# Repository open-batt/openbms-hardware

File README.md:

# OpenBMS

OpenBMS is an **open-source battery management system** for 2 to 7-cell Li-Ion and Li-Po battery packs. A fully integrated hardware and firmware solution for battery management and protection, providing:
-  **Fuel gauge** — measure battery capacity, state of charge, and state of health
-  **Learning algorithms** — learn battery behavior and adjust management accordingly
-  **Cell balancing** — keep multi-cell voltages in sync to prevent drift over time
-  **Protection** — guard against overcharging, overdischarging, overheating, and short circuits
-  **Communication** — talk to chargers, displays, microcontrollers, and other devices

<table>
  <tr>
    <td></td>
    <td></td>
  </tr>
</table>

## Rev B is out!
Schematic and layout updated, fixes applied

## Related repositories

[OpenBMS-firmware](https://github.com/open-batt/openbms-firmware)  
[OpenBMS-test-bench](https://github.com/open-batt/openbms-test-bench-hardware)  
[OpenBMS-studio](https://github.com/open-batt/openbms-studio)

## How OpenBMS fits into system?

Battery system consists of:
- **Li-ion/Li-Po battery** — your custom 2- to 7-cell battery
- **OpenBMS** — battery management system that handles fuel gauging, cell balancing, learning algorithms, overcharge/overdischarge/overheat protection, and communication with chargers and microcontrollers
- [**Test Bench**](https://github.com/open-batt/openbms-test-bench-hardware) — a 600W dissipative resistive load for easier BMS development and testing
- **Host** — I2C/CAN interfaces, wake-up signal, can be a microcontroller, computer, etc.
- **Charger** — your custom charger, usually a CC/CV charger adjusted to your battery voltage and current
- [**OpenBMS Studio**](https://github.com/open-batt/openbms-studio) — a PC software for configuring and monitoring the BMS, visualizing data, and updating firmware using UART communication

<br/>

<video width="100%" autoplay muted loop playsinline>
  <source src="images_videos/video_2.mp4" type="video/mp4" />
</video>

## ❤️ Funding

This project is funded through [NGI0 Commons Fund](https://nlnet.nl/commonsfund), a fund established by [NLnet](https://nlnet.nl) with financial support from the European Commission's [Next Generation Internet](https://ngi.eu) program. 

We are very grateful to the NLnet team for helping us on our path, and we encourage you too to apply and get funds to build your project! 🚀
Learn more at the [NLnet project page](https://nlnet.nl/project/OpenBMS).

## ⚠️ Status: Work in progress

| Module | Status |
|--------|--------|
| OpenBMS Schematics & PCB Layout Rev A| ✅ Done |
| OpenBMS Test Bench Schematic & PCB Layout | ✅ Done |
| Revision B (Hardware improvements) |  ✅ Done |
| BMS, Test Bench & Battery Tests |  🚧 In progress |
| Documentation & Final Release | 🚧 In progress |

## Features

- 🔋 Supports pack voltages up to 30V and continuous currents up to 16A.
- ⚡ State of Charge (SoC) estimation using coulomb counting
- 🩺 State of Health (SoH) monitoring with capacity fade tracking and internal resistance estimation
- 📊 Per-cell voltage monitoring with 24-bit resolution
- 🔌 Pack and cell overcurrent protection up to 20A hardware trip (adjustable threshold)
- 🛡️ Overvoltage and undervoltage protection (adjustable thresholds)
- 🔀 Passive cell balancing for up to 7 cells
- 🔵 Battery current measurement via precision shunt resistor
- 🌡️ NTC thermistor input for battery temperature monitoring
- 🌡️ On-board ambient temperature monitoring via MCU and ADC internal sensors
- 💾 Non-volatile storage of SoC, SoH, impedance, fault history, and charge profiles (EEPROM)
- 🚌 CAN bus communication interface (up to 1 Mbit/s)
- 🔗 I2C communication interface for host integration (SMBus compatible)
- 🖥️ UART debug interface
- 🔔 Wake-up input with power-on latch for low-power system control
- 🔋 Power-down mode quiescent current < 2 µA
- 🖥️ Based on STM32L431 ARM Cortex-M4 microcontroller
  
## Overview
First, a small introduction to the project structure:
```
+-------------+       +---------------------------+       +----------------+
|             |       |         OpenBMS           |       |                |
|   Battery   |       | - - - - - - - - - - - - - |       |     System     |
| 2-7S Li-Ion | cells |   +-------+   +-------+   |       |                |
| 2-7S Li-Po  |- - - >|   |  ADC  |   |  MCU  |   |<----->|    host/load   |
|             |       |   +-------+   +-------+   | comms |                |
|             |<=====>|   +-------+   +-------+   |<=====>|     Charger    |
|             |  pwr  |   | Power |   | FETs  |   |  pwr  |                |
+-------------+       |   +-------+   +-------+   |       +----------------+
                       +-----------+--------------+
```

OpenBMS and the battery are designed to be a single, inseparable unit. Ideally, it is
connected on the first day of the battery's life and stays throughout its entire lifetime.
This way, OpenBMS learns the battery's characteristics over time and continuously tracks
its state of health and other parameters.
 
It protects the battery from overcurrent, overvoltage, and undervoltage conditions, and
balances cells to maximize pack lifetime. State of charge estimation tells you exactly how
much energy you have left, while long-term health monitoring tells you when it's time to
replace the battery.
 
The battery communicates with the host system via CAN bus or I2C. Through OpenBMS, the battery can:
- Give energy to the system (discharge)
- Take energy from the system (charge)
 
OpenBMS can be easily described with the following block diagram:

```
+---------------------------------------------------------------------------------------------------------------+
|                                                  OpenBMS                                                      |
|                                                                                                               |
|  +-----------------------+     power     +-------------------+     power     +-------------------------+      |
|  |    Battery Input      |<=============>|  Switch Circuit   |<=============>|         Output          |      |
|  | - - - - - - - - - - - |               | - - - - - - - - - |               | - - - - - - - - - - - - |      |
|  | + XT60 pwr connector  |               | + Main NFETs      |               | + XT60 pwr connector    |      |
|  | + 8-pin JST (balancer)|               | + Precharge FETs  |               | + JST (I2C,CAN,WAKE_UP) |      |
|  | + 2-pin JST (NTC)     |               +--------+----------+               +-------------------------+      |
|  +-----------------------+                         |                                      ^                   |
|            |                                       | ctr signals                          | can, i2c, wake_up |
|            | cells                                 v                                      |                   |
|  +---------------------+       SPI      +-------------------------+                       |                   |
|  |    Analog Block     |<==============>|     Digital Block       |=======================+                   |
|  |     (ADS131M08)     |                | - - - - - - - - - - - - |                                           |
|  | - - - - - - - - - - |                | + STM32L431 (Cortex-M4) |                                           |
|  | + Cell voltage x7   |                | + EEPROM                |                                           |
|  | + Pack voltage      |                | + LED indicators        |                                           |
|  | + Current           |                | + SWD / UART debug      |                                           |
|  | + PFETs cell switch |                | + I2C / CANinterfaces   |                                           |
|  +---------------------+                +-------------------------+                                           |
|                                                     ^                                                         |
|                                                     | 3.3V, wake_up                                           |
|                                          +----------+---------+                                               |
|                                          | 3.3V Power Supply  |                                               |
|                                          | - - - - - - - - -  |                                               |
|                                          | + Buck converter   |                                               |
|                                          | + Enable latch     |                                               |
|                                          +--------------------+                                               |
|                                                                                                               |
+---------------------------------------------------------------------------------------------------------------+
```

## Characteristics

| Parameter                                    | Value                                             |
|----------------------------------------------|---------------------------------------------------|
| Cell count                                   | 2 to 7 cells                                      |
| Supported chemistries                        | Li-Ion, Li-Po                                     |
| Communication interfaces                     | CAN bus (up to 1 Mbit/s), I2C (SMBus compatible)  |
| Maximum pack voltage                         | 30.1V (7 cells × 4.3V)                            |
| Minimum pack voltage                         | 4V (2 cells × 2V)                                 |
| Maximum continuous current                   | 16A                                               |
| Maximum peak current                         | 20A (hardware trip)                               |
| Current consumption (active, 7-cell, max)    | 6mA                                               |
| Current consumption (active, 7-cell, typ)    | 4mA                                               |
| Current consumption (active, 2-cell, max)    | 19mA                                              |
| Current consumption (active, 2-cell, typ)    | 13mA                                              |
| Power-down quiescent current                 | < 2 µA                                            |
| Operating temperature range                  | -40°C to 85°C                                     |

## License

OpenBMS is licensed under the MIT license and CERN OHL-S v2.

Check [openbatt.dev](https://openbatt.dev) for more!

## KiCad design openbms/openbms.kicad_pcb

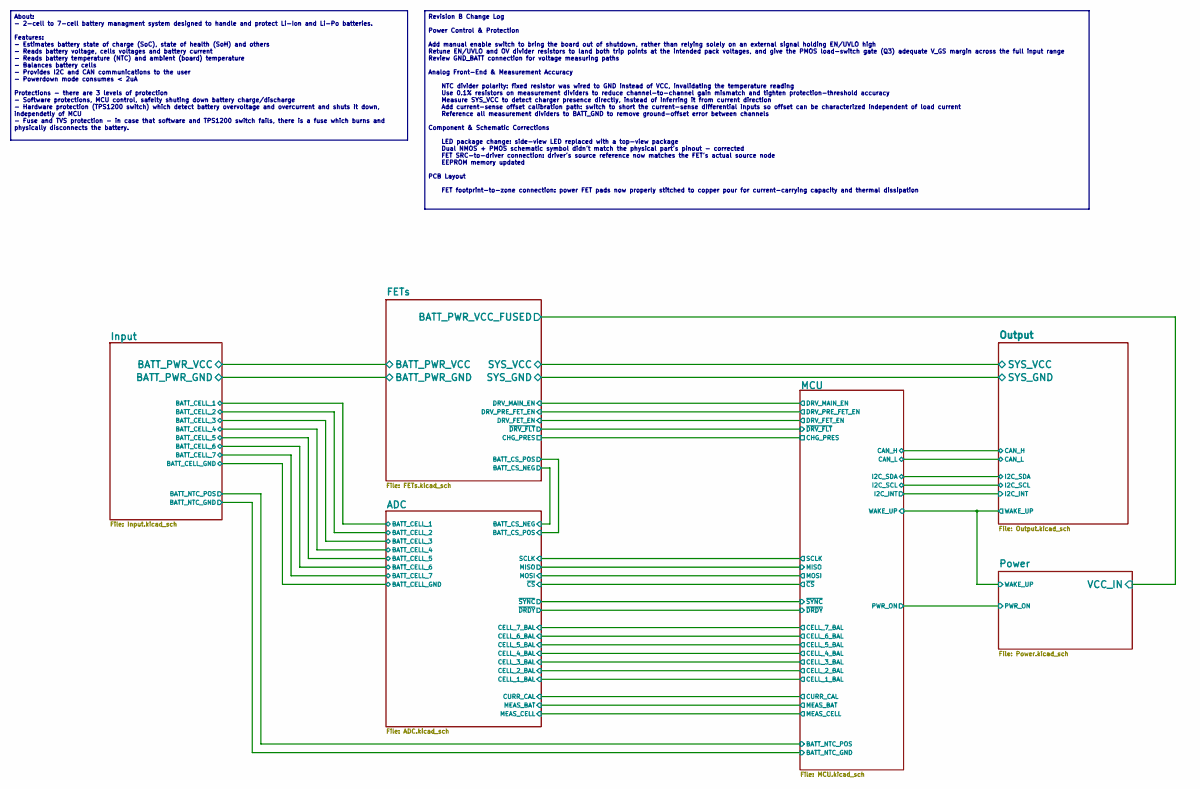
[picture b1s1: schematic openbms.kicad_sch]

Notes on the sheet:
About: - 2-cell to 7-cell battery managment system designed to handle and protect Li-Ion and Li-Po batteries. Features: - Estimates battery state of charge (SoC), state of health (SoH) and others - Reads battery voltage, cells voltages and battery current - Reads battery temperature (NTC) and ambie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
Revision B Change Log Power Control & Protection Add manual enable switch to bring the board out of shutdown, rather than relying solely on an external signal holding EN/UVLO high Retune EN/UVLO and OV divider resistors to land both trip points at the intended pack voltages, and give the PMOS load-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

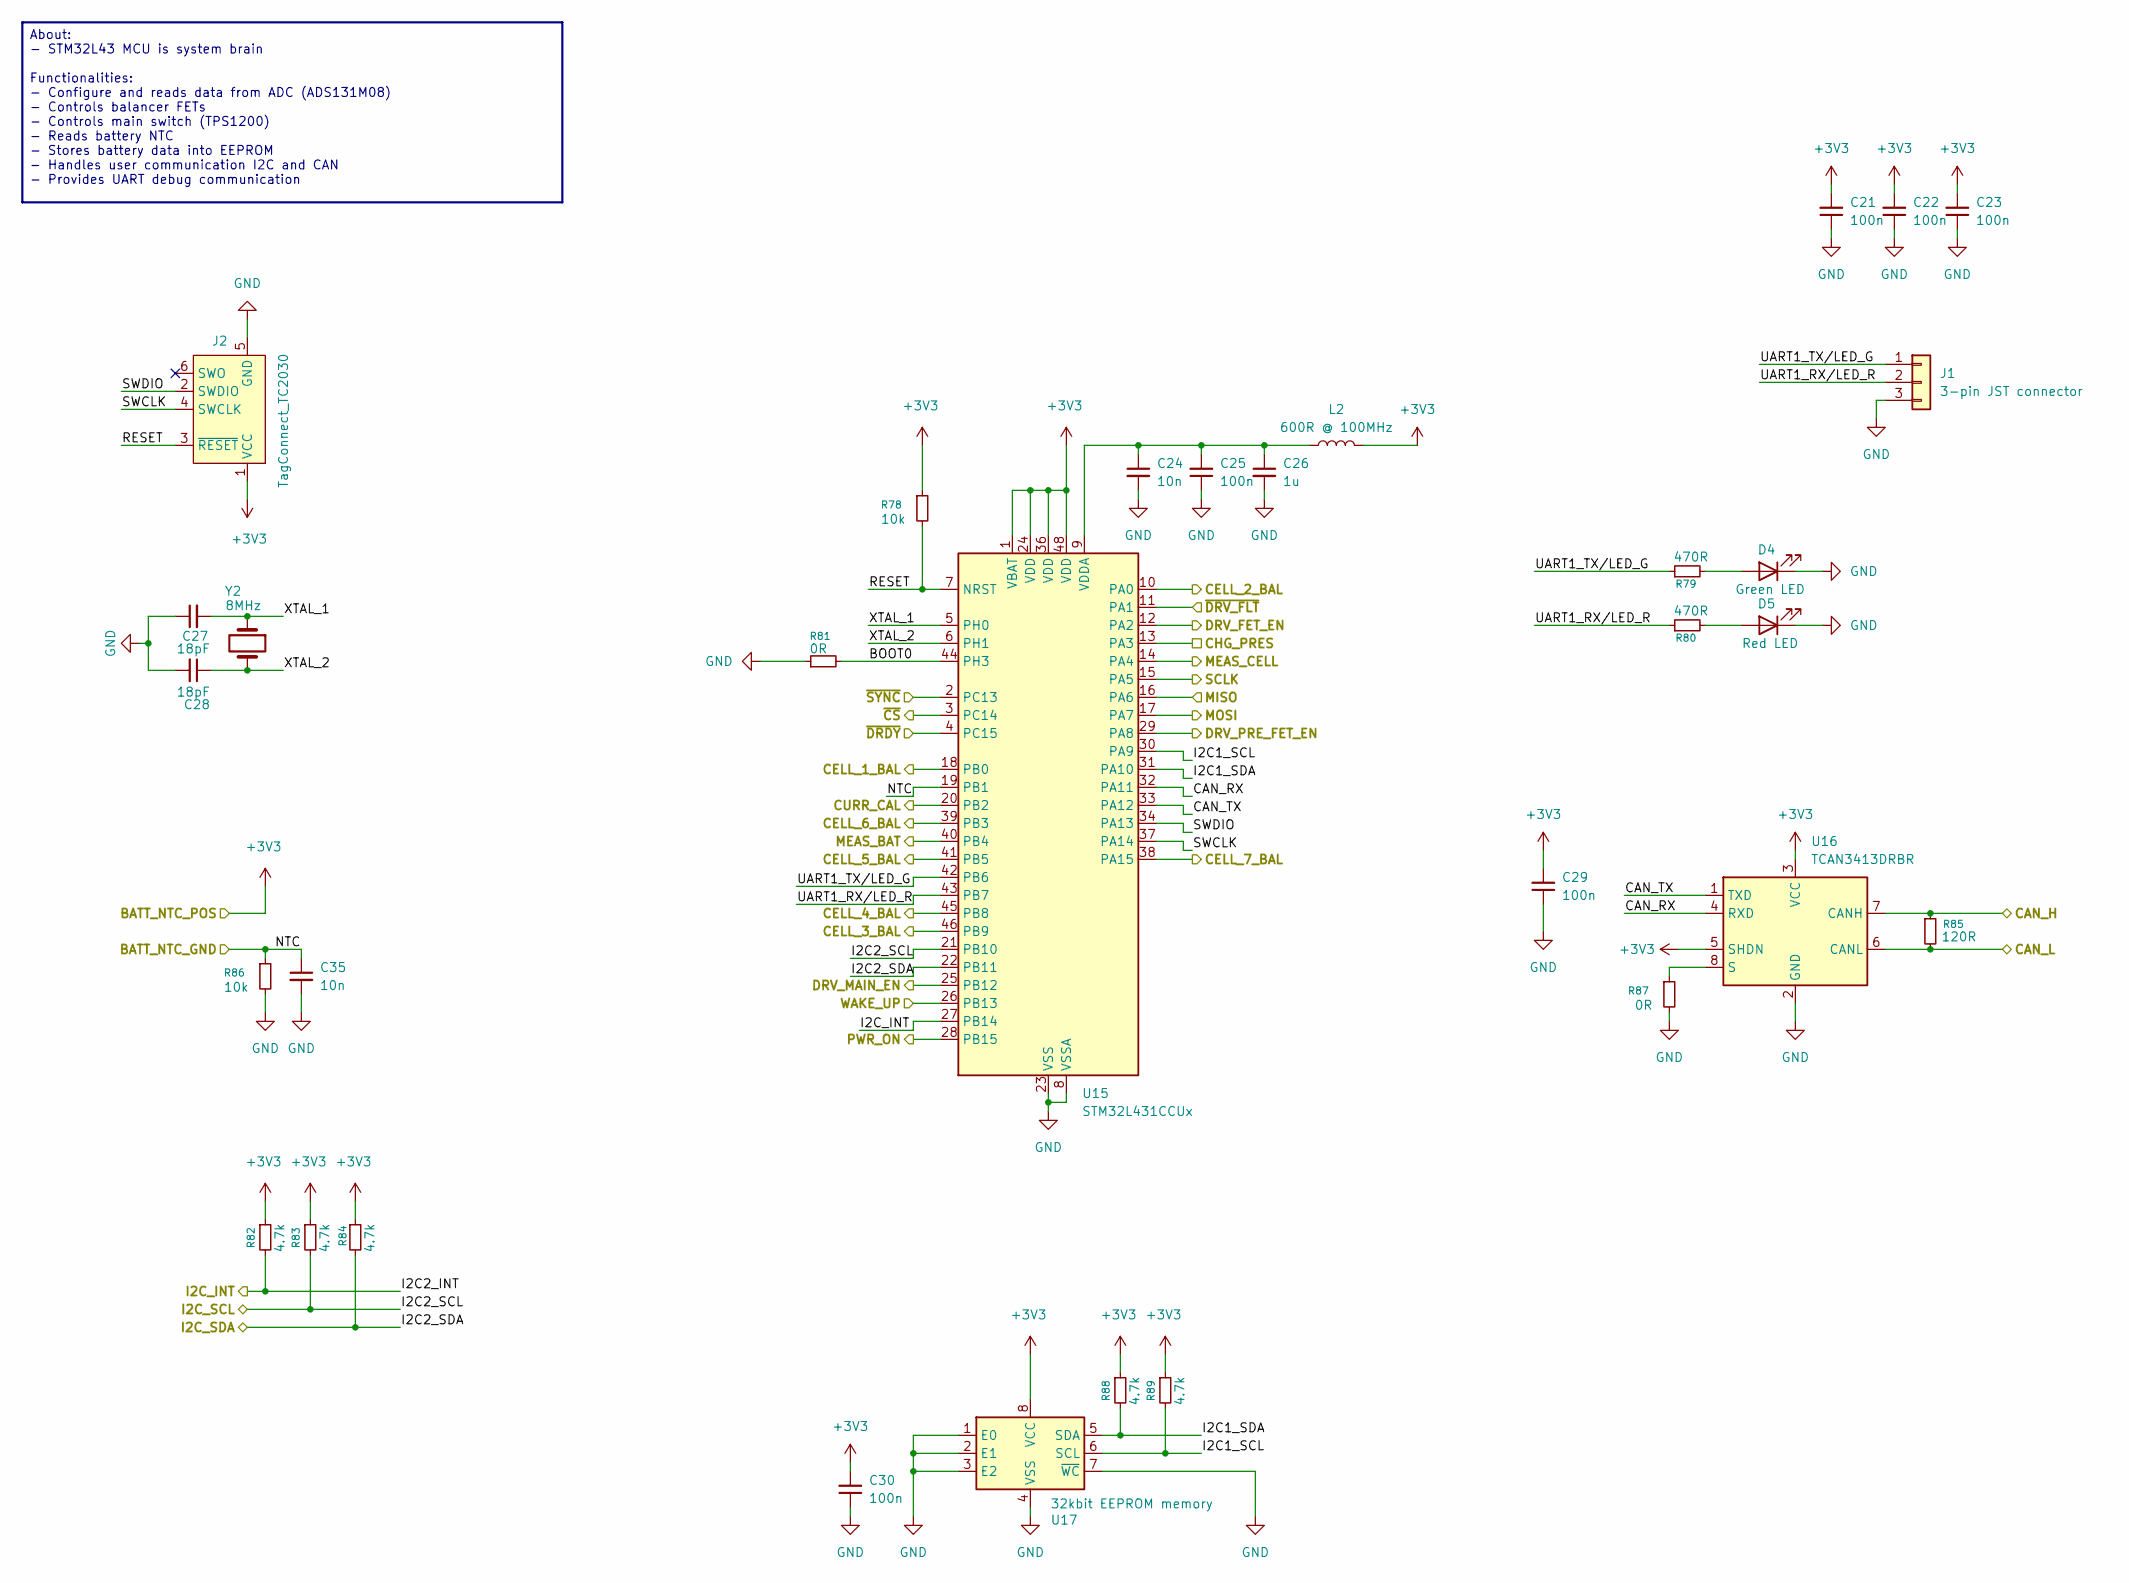
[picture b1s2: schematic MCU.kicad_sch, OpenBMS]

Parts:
C21, C22, C23, C25, C29, C30: 100n; C_0402_1005Metric; Manufacturer_Part_Number GRM155R71A104KA01D
C24, C35: 10n; C_0402_1005Metric; Manufacturer_Part_Number C0402C103K5REC7411
C26: 1u; C_0402_1005Metric; Manufacturer_Part_Number C0402C105K8PACTU
C27, C28: 18pF; C_0402_1005Metric; Manufacturer_Part_Number GRM1555C1H180JA01D
D4: Green LED; LED_0603_1608Metric; Manufacturer_Part_Number LTST-C190GKT
D5: Red LED; LED_0603_1608Metric; Manufacturer_Part_Number LTST-C190KRKT
J1: 3-pin JST connector; JST_GH_BM03B-GHS-TBT_1x03-1MP_P1.25mm_Vertical; Manufacturer_Part_Number BM03B-GHS-TBT
J2: TagConnect_TC2030; Tag-Connect_TC2030-IDC-FP_2x03_P1.27mm_Vertical
L2: 600R @ 100MHz; L_0402_1005Metric; Manufacturer_Part_Number BLM15PX601SN1D
R78, R86: 10k; R_0402_1005Metric; Manufacturer_Part_Number RMCF0402FT10K0
R79, R80: 470R; R_0402_1005Metric; Manufacturer_Part_Number RC0402FR-07470RL
R81, R87: 0R; R_0402_1005Metric; Manufacturer_Part_Number CR0402AJ/-000GAS
R82, R83, R84, R88, R89: 4.7k; R_0402_1005Metric; Manufacturer_Part_Number RC0402JR-074K7L
R85: 120R; R_0402_1005Metric; Manufacturer_Part_Number CRCW0402120RFKEDC
U15: STM32L431CCUx; QFN-48-1EP_7x7mm_P0.5mm_EP5.6x5.6mm; Manufacturer_Part_Number STM32L431CCU6TR
U16: TCAN3413DRBR; Manufacturer_Part_Number TCAN3413DRBR
U17: 32kbit EEPROM memory; SOIC-8_3.9x4.9mm_P1.27mm; Manufacturer_Part_Number M24256-DRMN8TP/K
Y2: 8MHz; ECS81921230QENTR; Manufacturer_Part_Number ECS-80-12-30Q-DS-TR

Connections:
+3V3: C21.2, C22.2, C23.2, C29.2, C30.2, J2.1 (VCC), L2.2, R78.1, R82.1, R83.1, R84.1, R88.1, R89.1, U15.1 (VBAT), U15.24 (VDD), U15.36 (VDD), U15.48 (VDD), U16.3 (VCC), U16.5 (SHDN), U17.8 (VCC); also elsewhere on the board
/ADC/CELL_1_BAL: U15.18 (PB0); also elsewhere on the board
/ADC/CELL_2_BAL: U15.10 (PA0); also elsewhere on the board
/ADC/CELL_3_BAL: U15.46 (PB9); also elsewhere on the board
/ADC/CELL_4_BAL: U15.45 (PB8); also elsewhere on the board
/ADC/CELL_5_BAL: U15.41 (PB5); also elsewhere on the board
/ADC/CELL_6_BAL: U15.39 (PB3); also elsewhere on the board
/ADC/CELL_7_BAL: U15.38 (PA15); also elsewhere on the board
/ADC/CURR_CAL: U15.20 (PB2); also elsewhere on the board
/ADC/MEAS_BAT: U15.40 (PB4); also elsewhere on the board
/ADC/MEAS_CELL: U15.14 (PA4); also elsewhere on the board
/ADC/MISO: U15.16 (PA6); also elsewhere on the board
/ADC/MOSI: U15.17 (PA7); also elsewhere on the board
/ADC/SCLK: U15.15 (PA5); also elsewhere on the board
/ADC/~CS: U15.3 (PC14); also elsewhere on the board
/ADC/~DRDY: U15.4 (PC15); also elsewhere on the board
/ADC/~SYNC: U15.2 (PC13); also elsewhere on the board
/FETs/CHG_PRES: U15.13 (PA3); also elsewhere on the board
/FETs/DRV_FET_EN: U15.12 (PA2); also elsewhere on the board
/FETs/DRV_MAIN_EN: U15.25 (PB12); also elsewhere on the board
/FETs/DRV_PRE_FET_EN: U15.29 (PA8); also elsewhere on the board
/FETs/~DRV_FLT: U15.11 (PA1); also elsewhere on the board
/MCU/BOOT0: R81.2, U15.44 (PH3)
/MCU/CAN_H: R85.1, U16.7 (CANH); also elsewhere on the board
/MCU/CAN_L: R85.2, U16.6 (CANL); also elsewhere on the board
/MCU/CAN_RX: U15.32 (PA11), U16.4 (RXD)
/MCU/CAN_TX: U15.33 (PA12), U16.1 (TXD)
/MCU/I2C1_SCL: R89.2, U15.30 (PA9), U17.6 (SCL)
/MCU/I2C1_SDA: R88.2, U15.31 (PA10), U17.5 (SDA)
/MCU/I2C2_INT: R82.2, U15.27 (PB14); also elsewhere on the board
/MCU/I2C2_SCL: R83.2, U15.21 (PB10); also elsewhere on the board
/MCU/I2C2_SDA: R84.2, U15.22 (PB11); also elsewhere on the board
/MCU/NTC: C35.1, R86.1, U15.19 (PB1); also elsewhere on the board
/MCU/PWR_ON: U15.28 (PB15); also elsewhere on the board
/MCU/RESET: J2.3 (~RESET), R78.2, U15.7 (NRST)
/MCU/SWCLK: J2.4 (SWCLK), U15.37 (PA14)
/MCU/SWDIO: J2.2 (SWDIO), U15.34 (PA13)
/MCU/WAKE_UP: U15.26 (PB13); also elsewhere on the board
/MCU/XTAL_1: C27.2, U15.5 (PH0), Y2.1
/MCU/XTAL_2: C28.1, U15.6 (PH1), Y2.2
GND: C21.1, C22.1, C23.1, C24.2, C25.1, C26.2, C27.1, C28.2, C29.1, C30.1, C35.2, D4.1 (K), D5.1 (K), J1.3, J2.5 (GND), R81.1, R86.2, R87.2, U15.8 (VSSA), U15.23 (VSS), U15.35 (VSS), U15.47 (VSS), U15.49 (VSS), U16.2 (GND), U17.1 (E0), U17.2 (E1), U17.3 (E2), U17.4 (VSS), U17.7 (~WC); also elsewhere on the board
unnamed: D4.2 (A), R79.2
unnamed: D5.2 (A), R80.2
unnamed: C24.1, C25.2, C26.1, L2.1, U15.9 (VDDA)
unnamed: R87.1, U16.8 (S)

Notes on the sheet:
About: - STM32L43 MCU is system brain Functionalities: - Configure and reads data from ADC (ADS131M08) - Controls balancer FETs - Controls main switch (TPS1200) - Reads battery NTC - Stores battery data into EEPROM - Handles user communication I2C and CAN - Provides UART debug communication

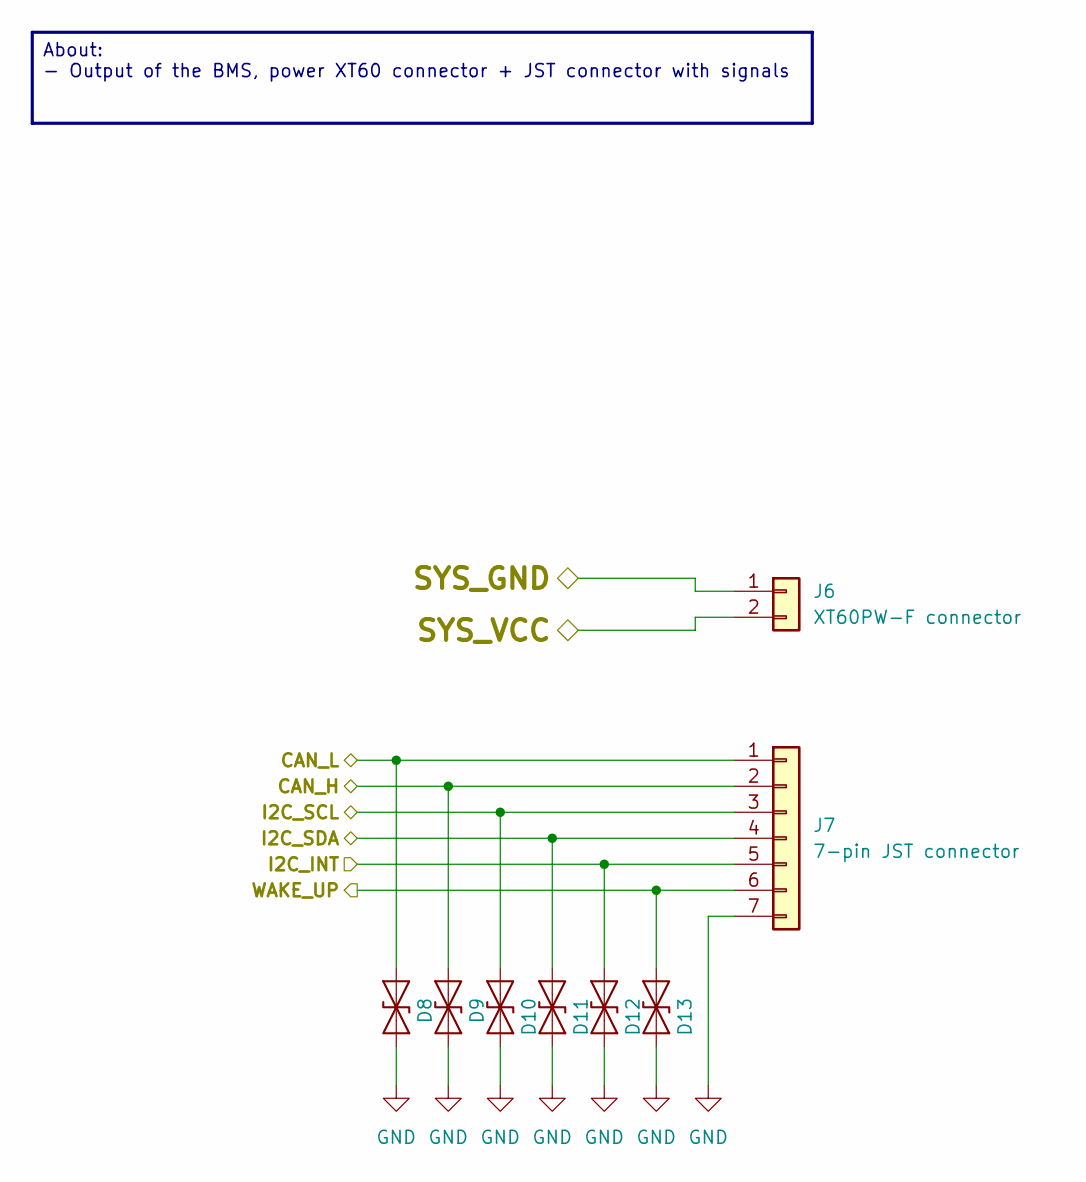
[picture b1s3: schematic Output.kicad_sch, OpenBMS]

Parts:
D8, D9, D10, D11, D12, D13: TVS diode DBLC03CIQ-7; D_SOD-323; Manufacturer_Part_Number DBLC03CIQ-7
J6: XT60PW-F connector; AMASS_XT60PW-F_1x02_P7.20mm_Horizontal; Manufacturer_Part_Number XT60PW-F
J7: 7-pin JST connector; JST_XH_S7B-XH-A_1x07_P2.50mm_Horizontal; Manufacturer_Part_Number S7B-XH-A

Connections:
/FETs/SYS_VCC: J6.2; also elsewhere on the board
/MCU/CAN_H: D9.1 (A1), J7.2; also elsewhere on the board
/MCU/CAN_L: D8.1 (A1), J7.1; also elsewhere on the board
/MCU/I2C2_INT: D12.1 (A1), J7.5; also elsewhere on the board
/MCU/I2C2_SCL: D10.1 (A1), J7.3; also elsewhere on the board
/MCU/I2C2_SDA: D11.1 (A1), J7.4; also elsewhere on the board
/MCU/WAKE_UP: D13.1 (A1), J7.6; also elsewhere on the board
GND: D8.2 (A2), D9.2 (A2), D10.2 (A2), D11.2 (A2), D12.2 (A2), D13.2 (A2), J7.7; also elsewhere on the board
SYS_GND: J6.1; also elsewhere on the board

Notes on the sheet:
About: - Output of the BMS, power XT60 connector + JST connector with signals

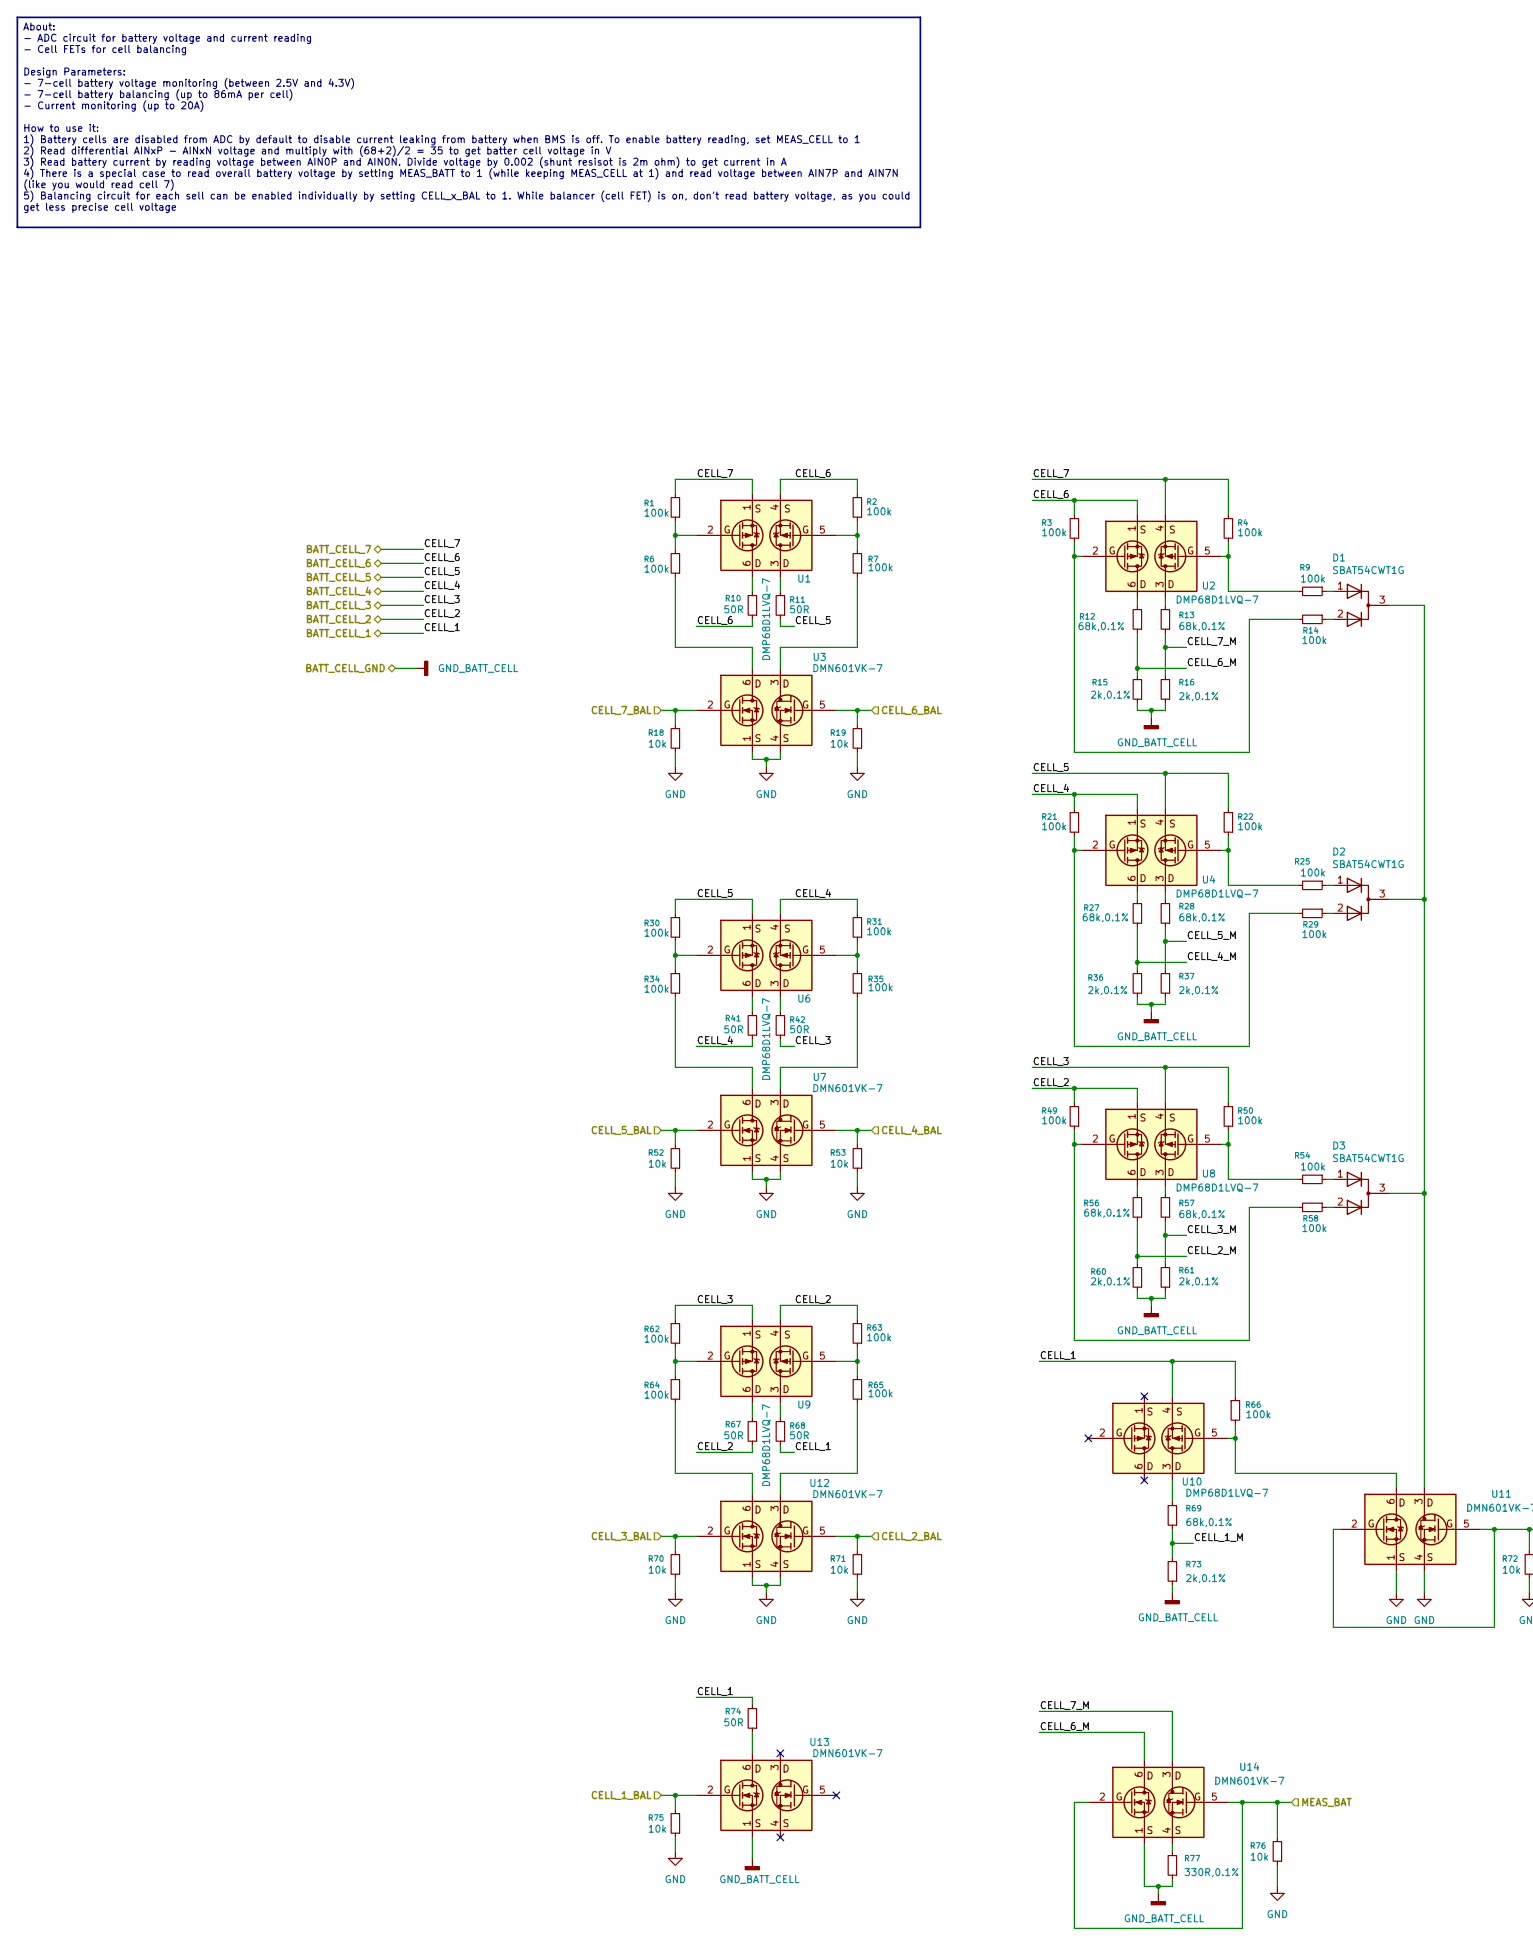
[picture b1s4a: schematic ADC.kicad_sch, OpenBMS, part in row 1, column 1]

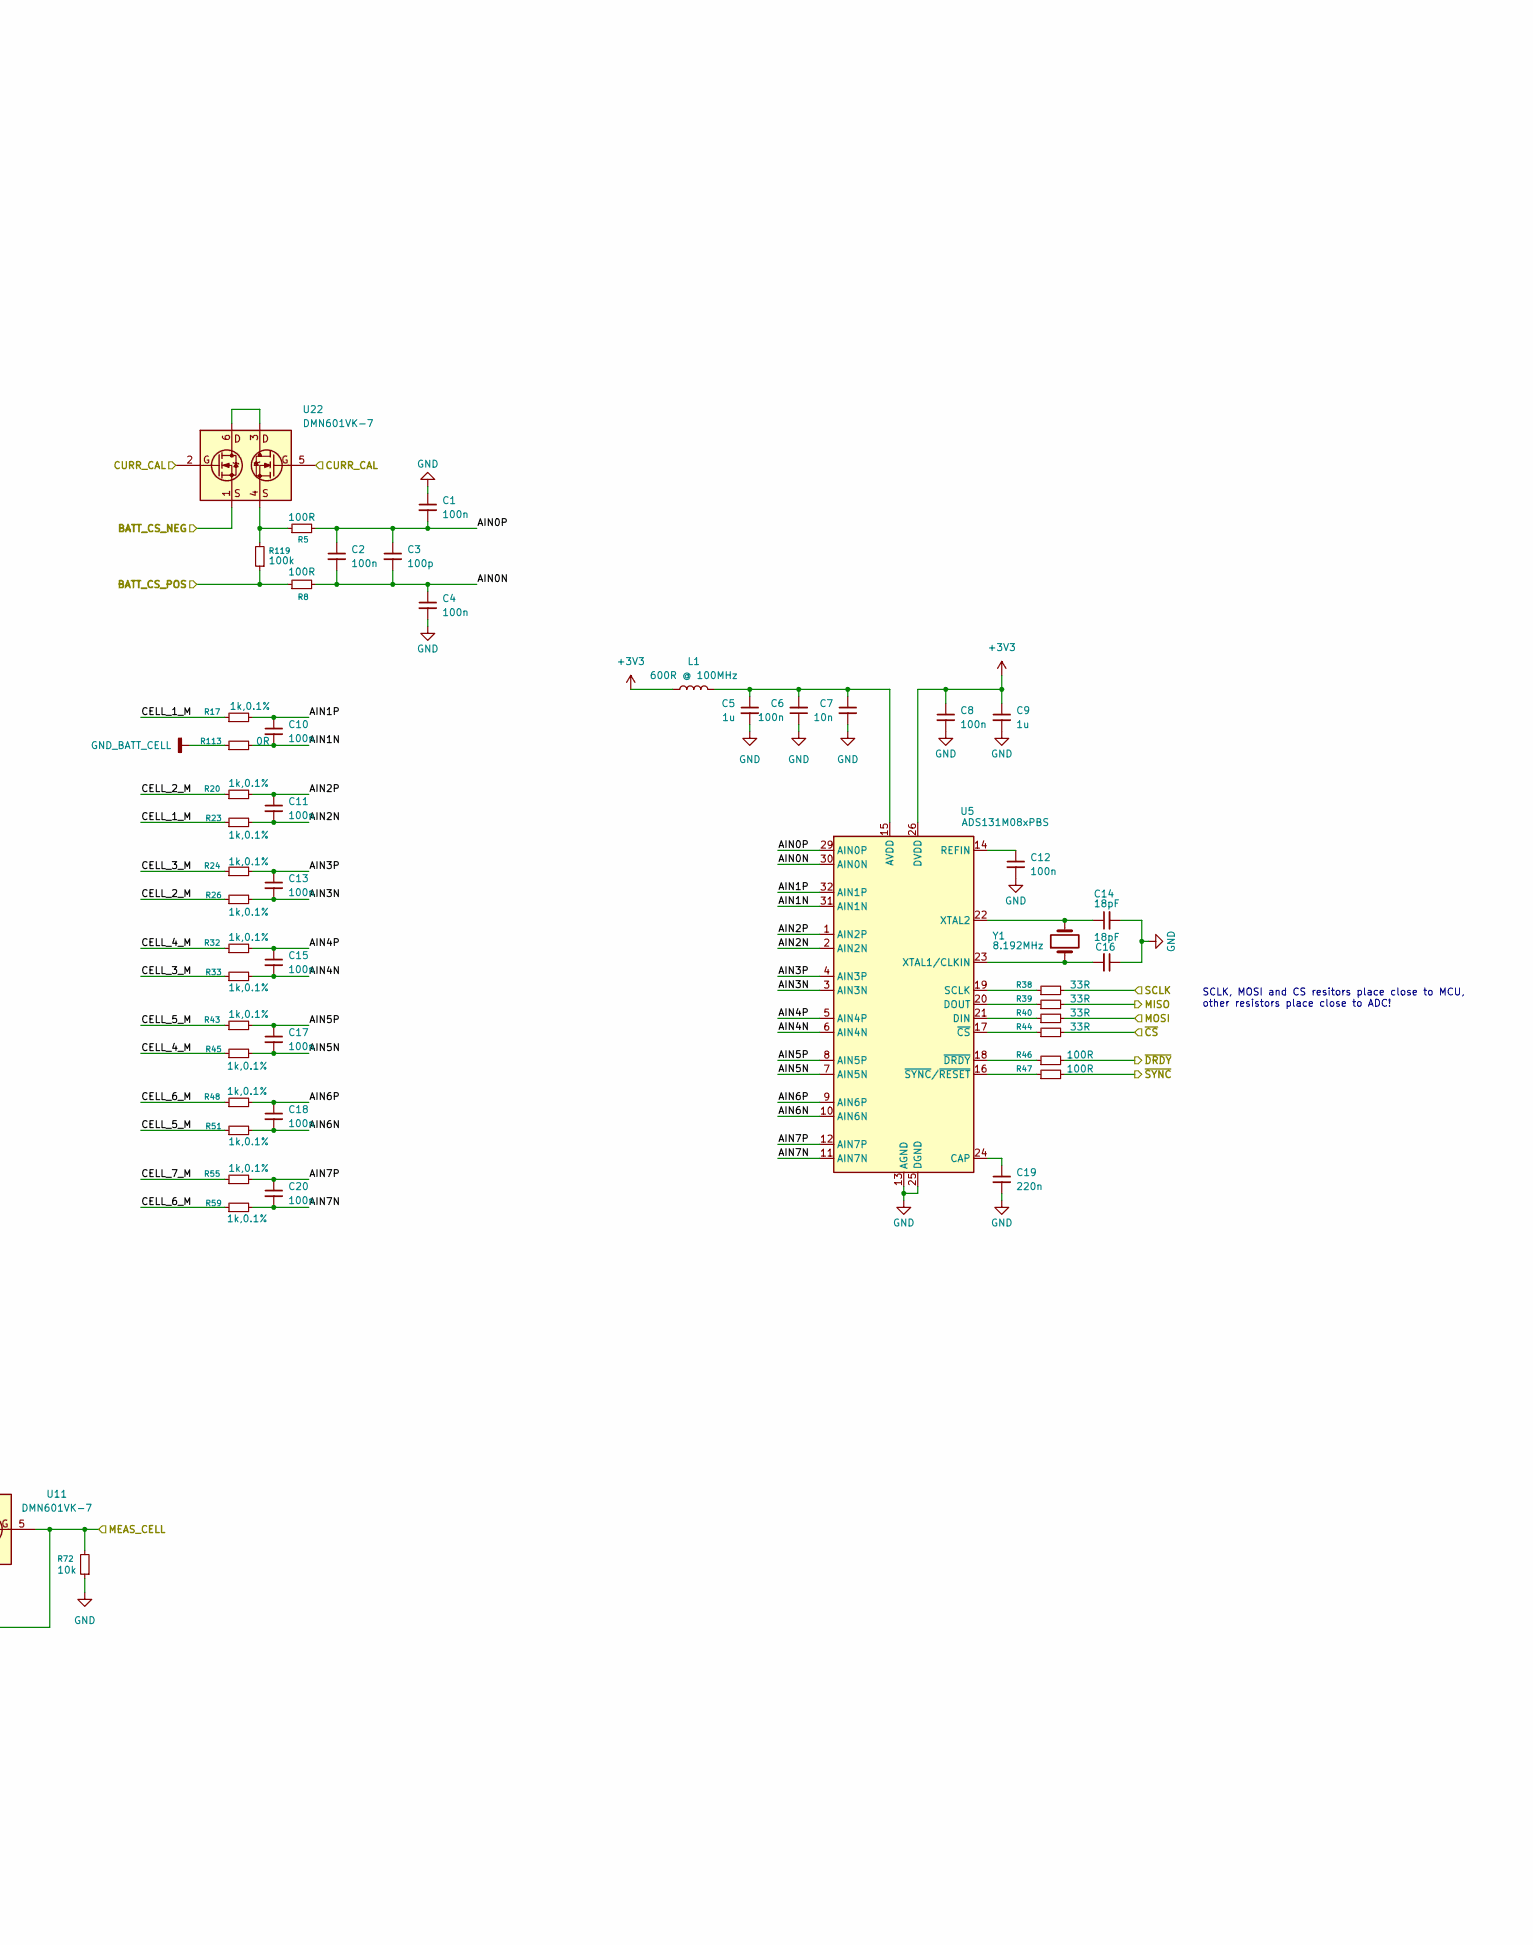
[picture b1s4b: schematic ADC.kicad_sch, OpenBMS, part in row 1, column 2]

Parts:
C1, C2, C4, C6, C8, C10, C11, C12, C13, C15, C17, C18, C20: 100n; C_0402_1005Metric; Manufacturer_Part_Number GRM155R71A104KA01D
C3: 100p; C_0402_1005Metric; Manufacturer_Part_Number CL05C101JB5NNNC
C5, C9: 1u; C_0402_1005Metric; Manufacturer_Part_Number C0402C105K8PACTU
C7: 10n; C_0402_1005Metric; Manufacturer_Part_Number C0402C103K5REC7411
C14, C16: 18pF; C_0402_1005Metric; Manufacturer_Part_Number GRM1555C1H180JA01D
C19: 220n; C_0402_1005Metric; Manufacturer_Part_Number GRM155R71A224KE01J
D1, D2, D3: SBAT54CWT1G; SOT-323_SC-70; Manufacturer_Part_Number SBAT54CWT1G
L1: 600R @ 100MHz; L_0402_1005Metric; Manufacturer_Part_Number BLM15PX601SN1D
R1, R2, R3, R4, R6, R7, R9, R14, R21, R22, R25, R29, R30, R31, R34, R35, R49, R50, R54, R58, R62, R63, R64, R65, R66, R119: 100k; R_0402_1005Metric; Manufacturer_Part_Number RC0402FR-07100KL
R5, R8: 100R; R_0402_1005Metric; Manufacturer_Part_Number RMCF0402FT100R
R10, R11, R41, R42, R67, R68, R74: 50R; R_2512_6332Metric; Manufacturer_Part_Number RNCL2512FT50R0
R12, R13, R27, R28, R56, R57, R69: 68k,0.1%; R_0402_1005Metric; Manufacturer_Part_Number RT0402BRD0768KL
R15, R16, R36, R37, R60, R61, R73: 2k,0.1%; R_0402_1005Metric; Manufacturer_Part_Number RT0402BRD072KL
R17, R20, R23, R24, R26, R32, R33, R43, R45, R48, R51, R55, R59: 1k,0.1%; R_0402_1005Metric; Manufacturer_Part_Number RT0402BRD071KL
R18, R19, R52, R53, R70, R71, R72, R75, R76: 10k; R_0402_1005Metric; Manufacturer_Part_Number RMCF0402FT10K0
R38, R39, R40, R44: 33R; R_0402_1005Metric; Manufacturer_Part_Number RC0402FR-0733RL
R46, R47: 100R; R_0402_1005Metric; Manufacturer_Part_Number RC0402FR-07100RL
R77: 330R,0.1%; R_0402_1005Metric; Manufacturer_Part_Number RT0402BRD07330RL
R113: 0R; R_0402_1005Metric; Manufacturer_Part_Number CR0402AJ/-000GAS
U1, U2, U4, U6, U8, U9, U10: DMP68D1LVQ-7; SOTFL50P162X60-6N; Manufacturer_Part_Number DMP68D1LVQ-7; Mouser Part Number 621-DMP68D1LVQ-7
U3, U7, U11, U12, U13, U14, U22: DMN601VK-7; SOTFL50P162X60-6N; Manufacturer_Part_Number DMN601VK-7
U5: ADS131M08xPBS; TQFP-32_5x5mm_P0.5mm; Manufacturer_Part_Number ADS131M08IPBS
Y1: 8.192MHz; ECS81921230QENTR; Manufacturer_Part_Number ECS-81.92-12-30Q-EN-TR

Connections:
+3V3: C8.1, C9.1, L1.2, U5.26 (DVDD); also elsewhere on the board
/ADC/AIN0N: C2.2, C3.2, C4.1, R8.2, U5.30 (AIN0N)
/ADC/AIN0P: C1.2, C2.1, C3.1, R5.2, U5.29 (AIN0P)
/ADC/AIN1N: C10.2, R113.2, U5.31 (AIN1N)
/ADC/AIN1P: C10.1, R17.2, U5.32 (AIN1P)
/ADC/AIN2N: C11.2, R23.2, U5.2 (AIN2N)
/ADC/AIN2P: C11.1, R20.2, U5.1 (AIN2P)
/ADC/AIN3N: C13.2, R26.2, U5.3 (AIN3N)
/ADC/AIN3P: C13.1, R24.2, U5.4 (AIN3P)
/ADC/AIN4N: C15.2, R33.2, U5.6 (AIN4N)
/ADC/AIN4P: C15.1, R32.2, U5.5 (AIN4P)
/ADC/AIN5N: C17.2, R45.2, U5.7 (AIN5N)
/ADC/AIN5P: C17.1, R43.2, U5.8 (AIN5P)
/ADC/AIN6N: C18.2, R51.2, U5.10 (AIN6N)
/ADC/AIN6P: C18.1, R48.2, U5.9 (AIN6P)
/ADC/AIN7N: C20.2, R59.2, U5.11 (AIN7N)
/ADC/AIN7P: C20.1, R55.2, U5.12 (AIN7P)
/ADC/BATT_CS_POS: R8.1, R119.1; also elsewhere on the board
/ADC/CELL_1: R66.1, R68.1, R74.2, U10.4; also elsewhere on the board
/ADC/CELL_1_BAL: R75.2, U13.2; also elsewhere on the board
/ADC/CELL_1_M: R17.1, R23.1, R69.1, R73.2
/ADC/CELL_2: R49.2, R63.2, R67.1, U8.1, U9.4; also elsewhere on the board
/ADC/CELL_2_BAL: R71.2, U12.5; also elsewhere on the board
/ADC/CELL_2_M: R20.1, R26.1, R56.1, R60.2
/ADC/CELL_3: R42.1, R50.2, R62.2, U8.4, U9.1; also elsewhere on the board
/ADC/CELL_3_BAL: R70.2, U12.2; also elsewhere on the board
/ADC/CELL_3_M: R24.1, R33.1, R57.1, R61.2
/ADC/CELL_4: R21.2, R31.2, R41.1, U4.1, U6.4; also elsewhere on the board
/ADC/CELL_4_BAL: R53.2, U7.5; also elsewhere on the board
/ADC/CELL_4_M: R27.1, R32.1, R36.2, R45.1
/ADC/CELL_5: R11.1, R22.2, R30.2, U4.4, U6.1; also elsewhere on the board
/ADC/CELL_5_BAL: R52.2, U7.2; also elsewhere on the board
/ADC/CELL_5_M: R28.1, R37.2, R43.1, R51.1
/ADC/CELL_6: R2.2, R3.2, R10.1, U1.4, U2.1; also elsewhere on the board
/ADC/CELL_6_BAL: R19.2, U3.5; also elsewhere on the board
/ADC/CELL_6_M: R12.1, R15.2, R48.1, R59.1, U14.6
/ADC/CELL_7: R1.2, R4.2, U1.1, U2.4; also elsewhere on the board
/ADC/CELL_7_BAL: R18.2, U3.2; also elsewhere on the board
/ADC/CELL_7_M: R13.1, R16.2, R55.1, U14.3
/ADC/CURR_CAL: U22.2, U22.5; also elsewhere on the board
/ADC/MEAS_BAT: R76.2, U14.2, U14.5; also elsewhere on the board
/ADC/MEAS_CELL: R72.2, U11.2, U11.5; also elsewhere on the board
/ADC/MISO: R39.2; also elsewhere on the board
/ADC/MOSI: R40.2; also elsewhere on the board
/ADC/SCLK: R38.2; also elsewhere on the board
/ADC/~CS: R44.2; also elsewhere on the board
/ADC/~DRDY: R46.2; also elsewhere on the board
/ADC/~SYNC: R47.2; also elsewhere on the board
GND: C1.1, C4.2, C5.2, C6.1, C7.2, C8.2, C9.2, C12.2, C14.2, C16.1, C19.2, R18.1, R19.1, R52.1, R53.1, R70.1, R71.1, R72.1, R75.1, R76.1, U3.1, U3.4, U5.13 (AGND), U5.25 (DGND), U5.27 (AGND), U5.28 (AGND), U7.1, U7.4, U11.1, U11.4, U12.1, U12.4; also elsewhere on the board
GND_BATT_CELL: R15.1, R16.1, R36.1, R37.1, R60.1, R61.1, R73.1, R77.1, R113.1, U13.1, U14.1; also elsewhere on the board
unnamed: D1.1 (A), R9.1
unnamed: D1.2 (A), R14.1
unnamed: D1.3 (K), D2.3 (K), D3.3 (K), U11.3
unnamed: D2.1 (A), R25.1
unnamed: D2.2 (A), R29.1
unnamed: D3.1 (A), R54.1
unnamed: D3.2 (A), R58.1
unnamed: R1.1, R6.2, U1.2
unnamed: R2.1, R7.2, U1.5
unnamed: R4.1, R9.2, U2.5
unnamed: R6.1, U3.6
unnamed: R7.1, U3.3
unnamed: R10.2, U1.6
unnamed: R11.2, U1.3
unnamed: R12.2, U2.6
unnamed: R13.2, U2.3
unnamed: R3.1, R14.2, U2.2
unnamed: R21.1, R29.2, U4.2
unnamed: R22.1, R25.2, U4.5
unnamed: R27.2, U4.6
unnamed: R28.2, U4.3
unnamed: R30.1, R34.2, U6.2
unnamed: R31.1, R35.2, U6.5
unnamed: R34.1, U7.6
unnamed: R35.1, U7.3
unnamed: R41.2, U6.6
unnamed: R42.2, U6.3
unnamed: R49.1, R58.2, U8.2
unnamed: R50.1, R54.2, U8.5
unnamed: R56.2, U8.6
unnamed: R57.2, U8.3
unnamed: R62.1, R64.2, U9.2
unnamed: R63.1, R65.2, U9.5
unnamed: R64.1, U12.6
unnamed: R65.1, U12.3
unnamed: R66.2, U10.5, U11.6
unnamed: R67.2, U9.6
unnamed: R68.2, U9.3
unnamed: R69.2, U10.3
unnamed: R74.1, U13.6
unnamed: R77.2, U14.4
unnamed: R5.1, R119.2, U22.4
unnamed: C5.1, C6.2, C7.1, L1.1, U5.15 (AVDD)
unnamed: C19.1, U5.24 (CAP)
unnamed: R40.1, U5.21 (DIN)
unnamed: R39.1, U5.20 (DOUT)
unnamed: C12.1, U5.14 (REFIN)
unnamed: R38.1, U5.19 (SCLK)
unnamed: C16.2, U5.23 (XTAL1/CLKIN), Y1.1
unnamed: C14.1, U5.22 (XTAL2), Y1.2
unnamed: R44.1, U5.17 (~CS)
unnamed: R46.1, U5.18 (~DRDY)
unnamed: R47.1, U5.16 (~SYNC/~RESET)
unnamed: U22.3, U22.6
SYS_GND: U22.1; also elsewhere on the board

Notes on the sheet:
SCLK, MOSI and CS resitors place close to MCU, other resistors place close to ADC!
About: - ADC circuit for battery voltage and current reading - Cell FETs for cell balancing Design Parameters: - 7-cell battery voltage monitoring (between 2.5V and 4.3V) - 7-cell battery balancing (up to 86mA per cell) - Current monitoring (up to 20A) How to use it: 1) Battery cells are disabled f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

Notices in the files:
README.md:
License: MIT
License: CERN-OHL-S-v2
